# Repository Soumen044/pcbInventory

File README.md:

# pcbInventory
Includes all self designed pcb's

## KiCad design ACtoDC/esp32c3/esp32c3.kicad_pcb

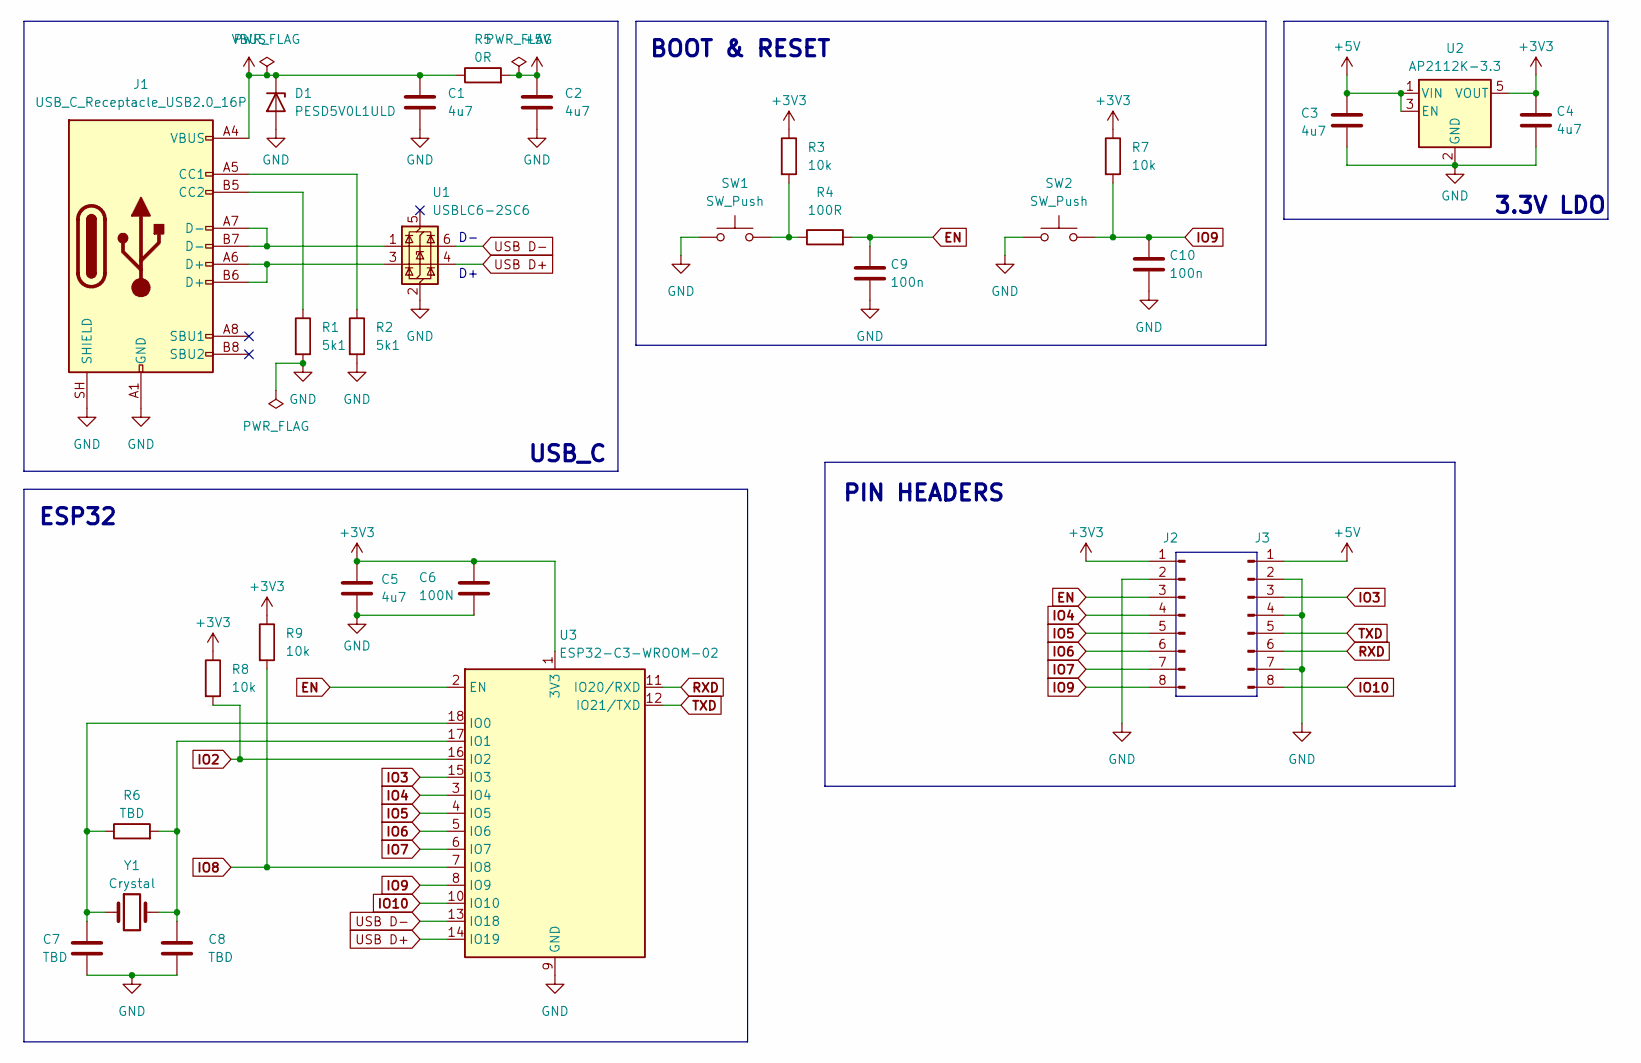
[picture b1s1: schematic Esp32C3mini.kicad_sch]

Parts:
C1, C2, C3, C4, C5: 4u7; C_0805_2012Metric
C6: 100N; C_0402_1005Metric
C7, C8: TBD; C_0201_0603Metric
C9, C10: 100n; C_0805_2012Metric
D1: PESD5V0L1ULD; D_SOD-882D
J1: USB_C_Receptacle_USB2.0_16P; USB_C_Receptacle_G-Switch_GT-USB-7010ASV
J2, J3: Conn_01x08_Pin; PinHeader_1x08_P2.54mm_Vertical
R1, R2: 5k1; R_0402_1005Metric
R3, R7, R8, R9: 10k; R_0402_1005Metric
R4: 100R; R_0402_1005Metric
R5: 0R; R_0805_2012Metric
R6: TBD; R_0201_0603Metric
SW1, SW2: SW_Push; SW_SPST_B3U-1000P
U1: USBLC6-2SC6; SOT-23-6
U2: AP2112K-3.3; SOT-23-5
U3: ESP32-C3-WROOM-02
Y1: Crystal; Crystal_SMD_3215-2Pin_3.2x1.5mm

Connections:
+3V3: C4.1, C5.1, C6.1, J2.1, R3.1, R7.1, R8.1, R9.1, U2.5 (VOUT), U3.1 (3V3)
+5V: C2.1, C3.1, J3.1, R5.2, U2.1 (VIN), U2.3 (EN)
EN: C9.1, J2.3, R4.2, U3.2 (EN)
GND: C1.2, C2.2, C3.2, C4.2, C5.2, C6.2, C7.2, C8.2, C9.2, C10.2, D1.2 (A), J1.A1 (GND), J1.A12 (GND), J1.B1 (GND), J1.B12 (GND), J1.SH (SHIELD), J2.2, J3.2, J3.4, J3.7, R1.2, R2.2, SW1.1, SW2.1, U1.2 (GND), U2.2 (GND), U3.9 (GND), U3.19 (GND)
IO2: R8.2, U3.16 (IO2)
IO3: J3.3, U3.15 (IO3)
IO4: J2.4, U3.3 (IO4)
IO5: J2.5, U3.4 (IO5)
IO6: J2.6, U3.5 (IO6)
IO7: J2.7, U3.6 (IO7)
IO8: R9.2, U3.7 (IO8)
IO9: C10.1, J2.8, R7.2, SW2.2, U3.8 (IO9)
IO10: J3.8, U3.10 (IO10)
unnamed: J1.A5 (CC1), R2.1
unnamed: J1.B5 (CC2), R1.1
unnamed: J1.A6 (D+), J1.B6 (D+), U1.3 (I/O2)
unnamed: J1.A7 (D-), J1.B7 (D-), U1.1 (I/O1)
unnamed: R3.2, R4.1, SW1.2
unnamed: C7.1, R6.1, U3.18 (IO0), Y1.1
unnamed: C8.1, R6.2, U3.17 (IO1), Y1.2
RXD: J3.6, U3.11 (IO20/RXD)
TXD: J3.5, U3.12 (IO21/TXD)
USB D+: U1.4 (I/O2), U3.14 (IO19)
USB D-: U1.6 (I/O1), U3.13 (IO18)
VBUS: C1.1, D1.1 (K), J1.A4 (VBUS), J1.A9 (VBUS), J1.B4 (VBUS), J1.B9 (VBUS), R5.1

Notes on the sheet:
3.3V LDO
ESP32
USB_C
BOOT & RESET
PIN HEADERS

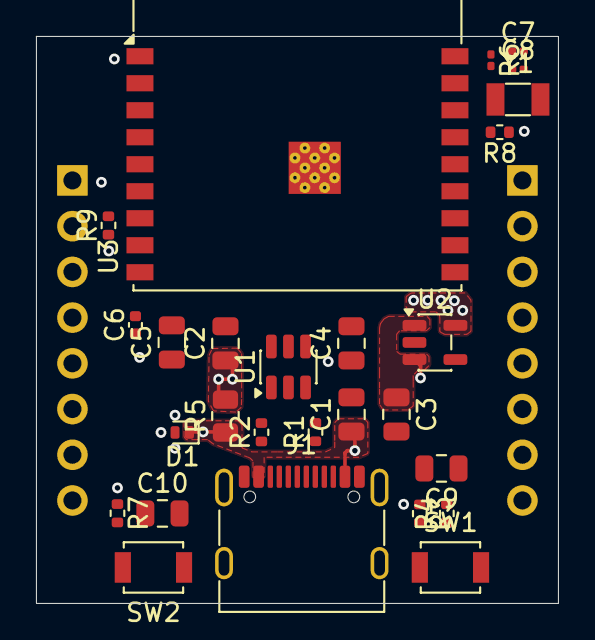
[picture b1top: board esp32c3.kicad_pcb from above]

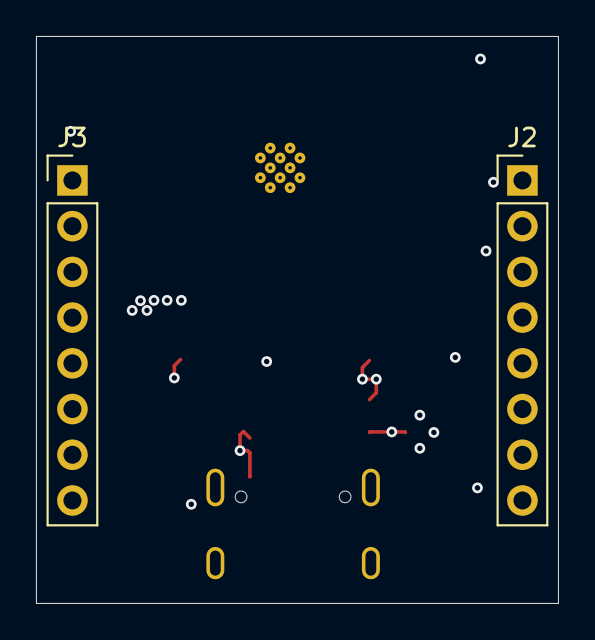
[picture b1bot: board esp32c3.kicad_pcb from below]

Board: 4 copper layers, 29.0 x 31.5 mm, 29 parts (2 on the bottom side), 25 nets.

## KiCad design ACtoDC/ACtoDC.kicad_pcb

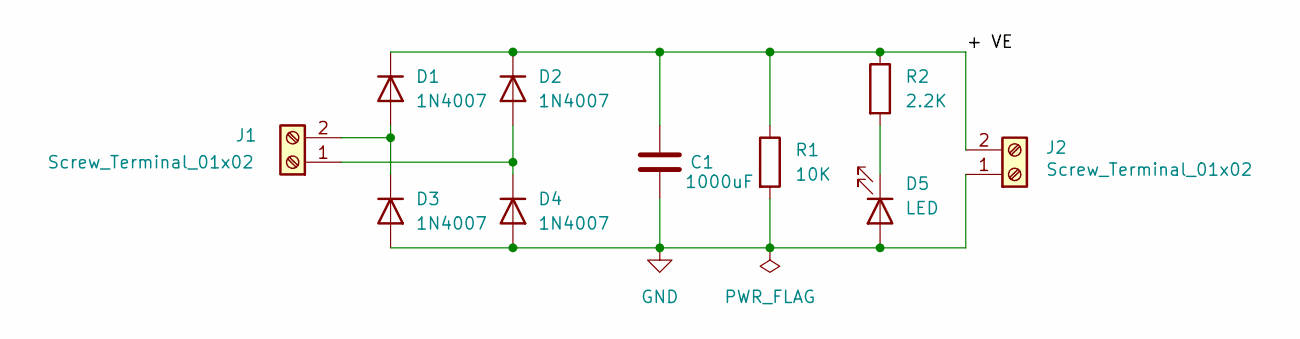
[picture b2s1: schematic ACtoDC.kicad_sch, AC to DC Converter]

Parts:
C1: 1000uF; C_Radial_D8.0mm_H11.5mm_P3.50mm
D1, D2, D3, D4: 1N4007; D_DO-41_SOD81_P10.16mm_Horizontal
D5: LED; LED_D5.0mm
J1, J2: Screw_Terminal_01x02; TerminalBlock_Xinya_XY308-2.54-2P_1x02_P2.54mm_Horizontal
R1: 10K; R_Axial_DIN0204_L3.6mm_D1.6mm_P7.62mm_Horizontal
R2: 2.2K; R_Axial_DIN0204_L3.6mm_D1.6mm_P7.62mm_Horizontal

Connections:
/+ VE: C1.1, D1.1 (K), D2.1 (K), J2.2, R1.1, R2.1
GND: C1.2, D3.2 (A), D4.2 (A), D5.2 (A), J2.1, R1.2
unnamed: D1.2 (A), D3.1 (K), J1.2
unnamed: D2.2 (A), D4.1 (K), J1.1
unnamed: D5.1 (K), R2.2

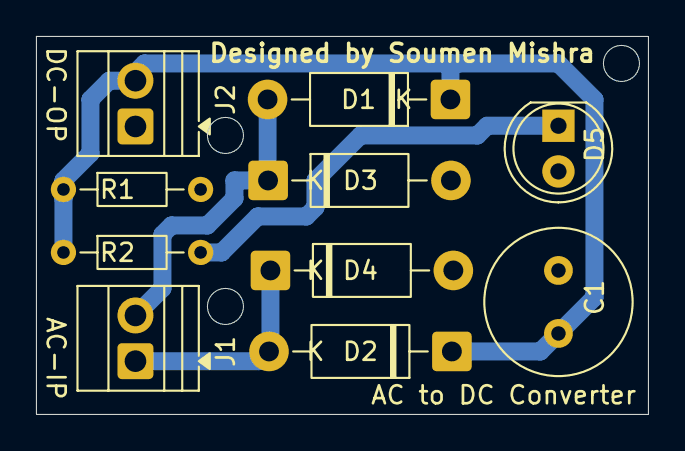
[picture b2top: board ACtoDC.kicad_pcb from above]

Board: 2 copper layers, 34.0 x 21.0 mm, 10 parts (0 on the bottom side), 5 nets.
